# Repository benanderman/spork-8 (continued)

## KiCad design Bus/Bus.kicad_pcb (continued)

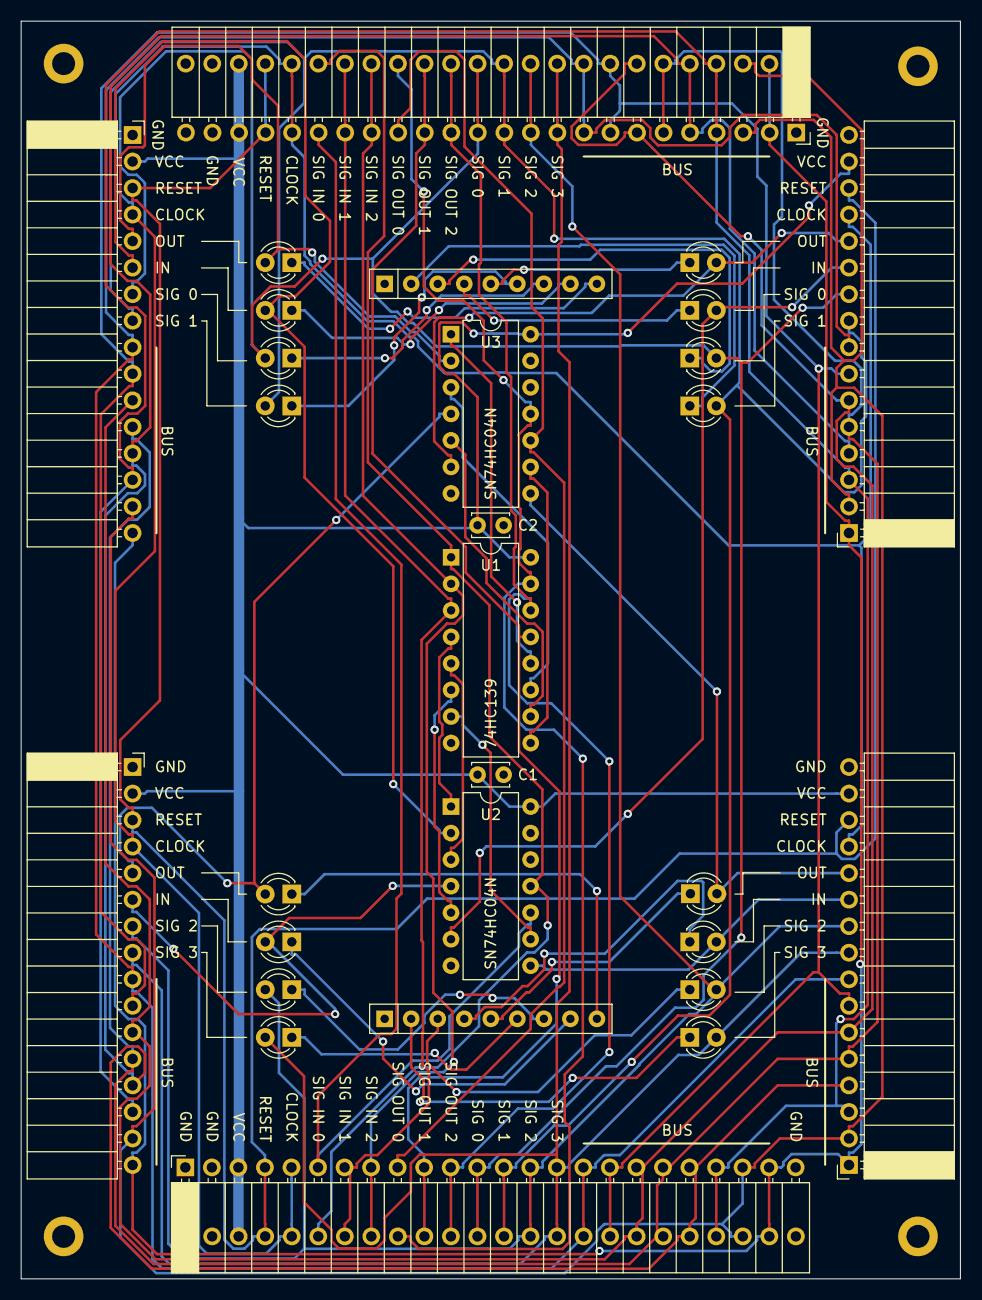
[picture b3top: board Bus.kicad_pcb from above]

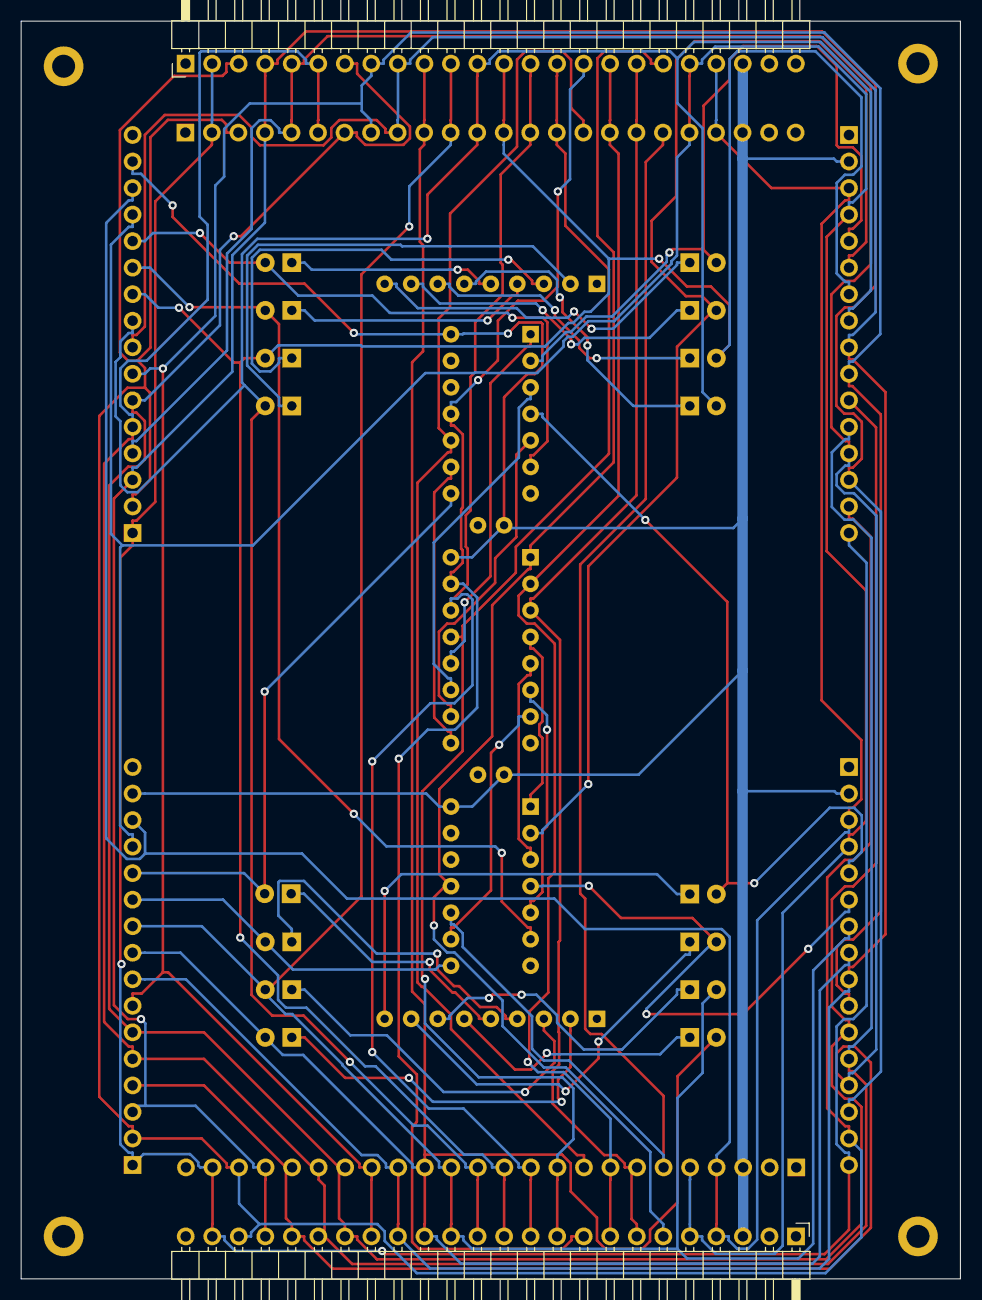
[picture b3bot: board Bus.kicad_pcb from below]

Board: 4 copper layers, 89.9 x 120.4 mm, 35 parts (2 on the bottom side), 56 nets.

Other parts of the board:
HOLE1, HOLE2, HOLE3, HOLE4: MountingHole_2.2mm_M2_DIN965_Pad

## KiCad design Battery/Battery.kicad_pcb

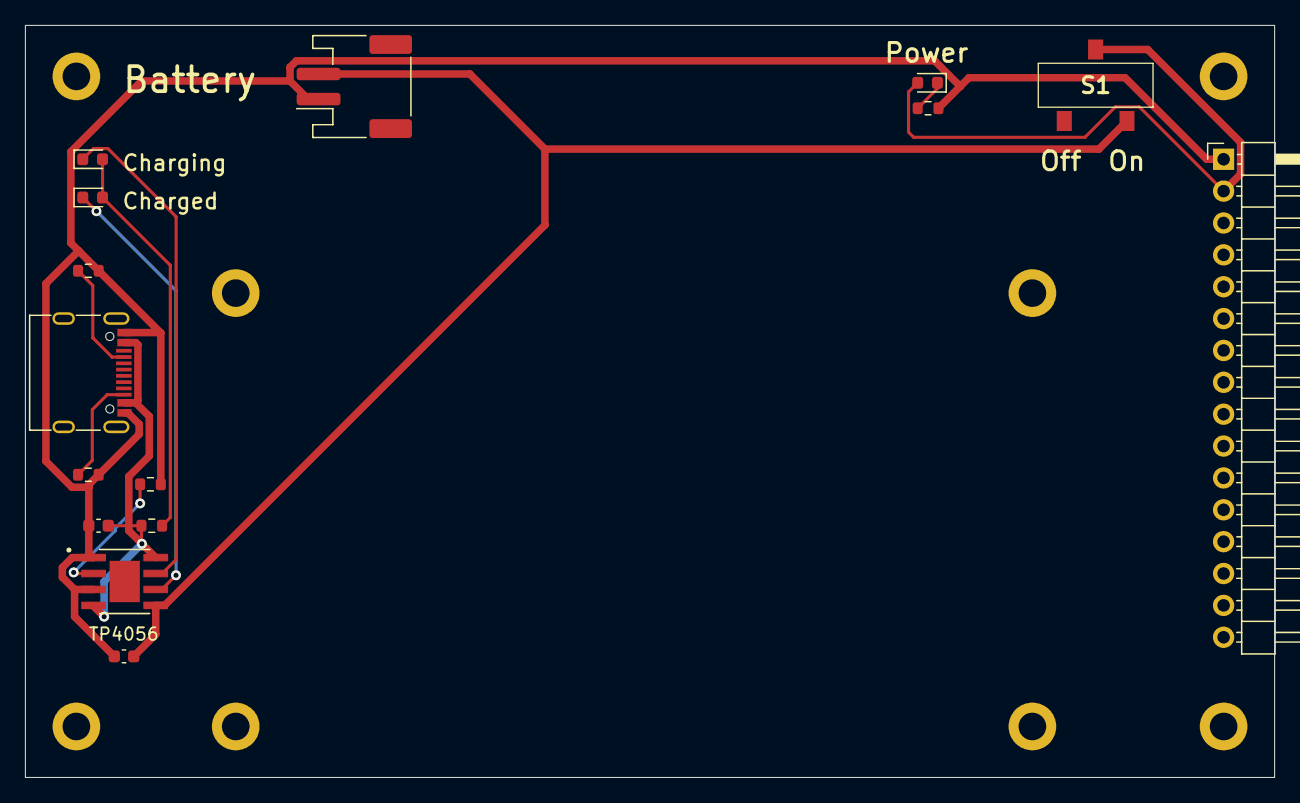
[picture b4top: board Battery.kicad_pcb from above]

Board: 2 copper layers, 99.6 x 59.9 mm, 23 parts (0 on the bottom side), 11 nets.

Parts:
BT1: Battery; JST_PH_S2B-PH-SM4-TB_1x02-1MP_P2.00mm_Horizontal
C1, C2: 10uF; C_0603_1608Metric
D1: GREEN; LED_0603_1608Metric
D2: RED; LED_0603_1608Metric
D3: LED; LED_0603_1608Metric
HOLE1, HOLE2, HOLE3, HOLE4, HOLE5, HOLE6, HOLE7, HOLE8: MountingHole_2.2mm_M2_DIN965_Pad
J1: Conn_01x16; PinHeader_1x16_P2.54mm_Horizontal
J4: USB_C_Receptacle_PowerOnly_6P; USB_C_Receptacle_G-Switch_GT-USB-7010ASV
R1: 1.2k; R_0603_1608Metric
R2, R5: 10k; R_0603_1608Metric
R3, R4: 5.1k; R_0603_1608Metric
S1: SS-3235D-03-L2; SS3235D03L2
U1: TP4056; SOP127P600X175-9N

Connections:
GND: BT1.1, C1.2, C2.2, J1.1, J4.A12 (GND), J4.B12 (GND), R1.1, R3.1, R4.1, R5.1, U1.1 (TEMP), U1.3 (GND)
unnamed: BT1.2, C2.1, S1.3, U1.5 (BAT)
unnamed: D1.2 (A), D2.2 (A), R2.1
unnamed: D1.1 (K), U1.6 (~STDBY)
unnamed: D2.1 (K), U1.7 (~CHRG)
unnamed: D3.1 (K), R5.2
unnamed: J4.A5 (CC1), R4.2
unnamed: J4.B5 (CC2), R3.2
unnamed: C1.1, J4.A9 (VBUS), J4.B9 (VBUS), R2.2, U1.4 (VCC), U1.8 (CE)
unnamed: R1.2, U1.2 (PROG)
VCC: D3.2 (A), J1.2, S1.2

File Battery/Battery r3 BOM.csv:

Designator,Comment,Footprint,LCSC Part Number
BT1,Battery,JST_PH_S2B-PH-SM4-TB_1x02-1MP_P2.00mm_Horizontal,C295747
"C1, C2",10uF,0603,C19702
D1,GREEN,0603,C965804
D2,RED,0603,C2286
D3,LED,0603,C72041
J1,Conn_01x16,PinHeader_1x16_P2.54mm_Horizontal,
J4,USB_C_Receptacle_PowerOnly_6P,USB_C_Receptacle_G-Switch_GT-USB-7010ASV,C2988369
R1,1.2k,0603,C22765
R2,10k,0603,C25804
"R3, R4",5.1k,0603,C23186
R5,10k,0603,C25804
S1,SS-3235D-03-L2,SS3235D03L2,C381097
U1,TP4056,SOP127P600X175-9N,C16581

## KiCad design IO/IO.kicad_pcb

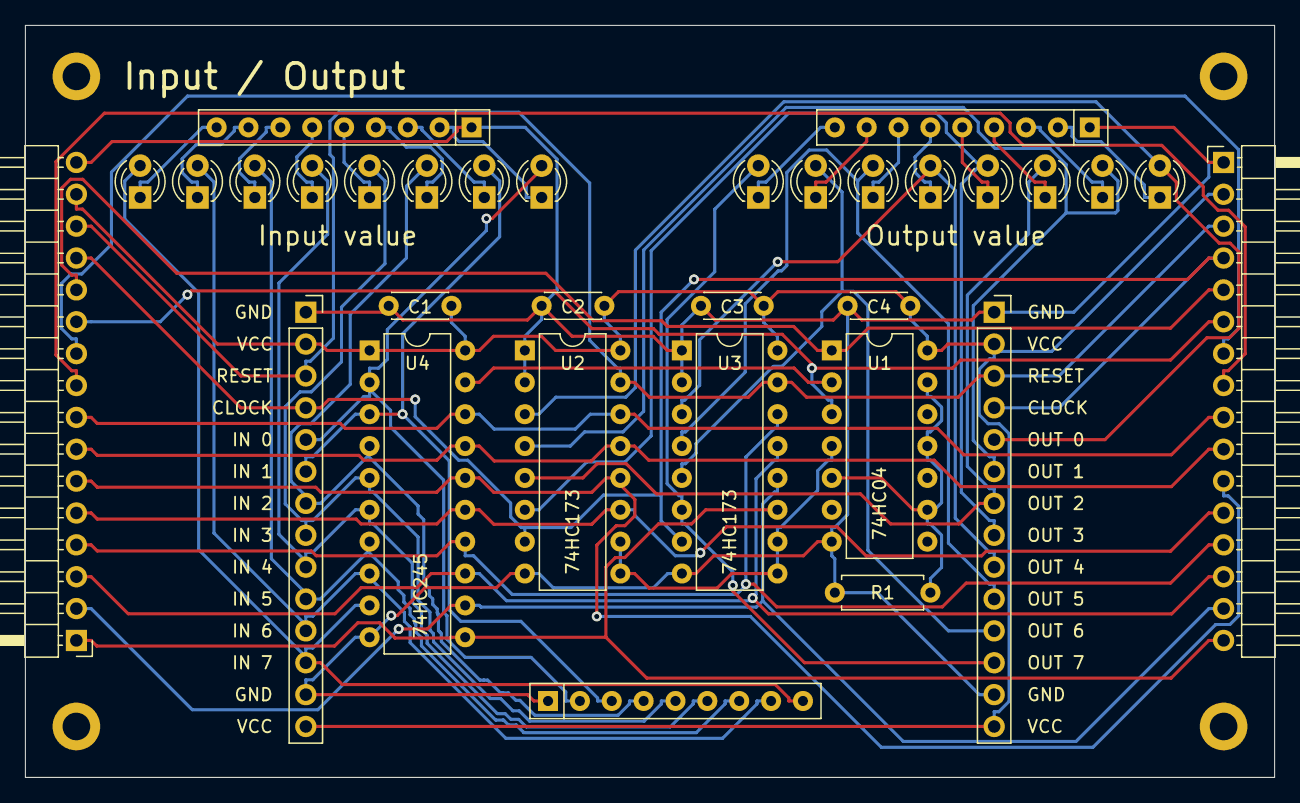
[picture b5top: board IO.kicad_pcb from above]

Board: 2 copper layers, 99.6 x 59.9 mm, 36 parts (0 on the bottom side), 51 nets.

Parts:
C1, C2, C3, C4: 100nF; C_Disc_D4.3mm_W1.9mm_P5.00mm
D1, D2, D3, D4, D5, D6, D7, D8, D9, D10, D11, D12, D13, D14, D15, D16: LED; LED_D3.0mm_Clear
HOLE1, HOLE2, HOLE3, HOLE4: MountingHole_2.2mm_M2_DIN965_Pad
J1, J2: Conn_01x16; PinHeader_1x16_P2.54mm_Horizontal
J3, J4: Conn_01x14; PinSocket_1x14_P2.54mm_Vertical
R1: 10k; R_Axial_DIN0207_L6.3mm_D2.5mm_P7.62mm_Horizontal
RN1, RN2: 1k; R_Array_SIP9
RN3: 100k; R_Array_SIP9
U1: 74HC04; DIP-14_W7.62mm
U2, U3: 74HC173; DIP-16_W7.62mm
U4: 74HC245; DIP-20_W7.62mm

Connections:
BUS0: J1.9, J2.8, U2.14 (D0), U4.18 (B0)
BUS1: J1.10, J2.7, U2.13 (D1), U4.17 (B1)
BUS2: J1.11, J2.6, U2.12 (D2), U4.16 (B2)
BUS3: J1.12, J2.5, U2.11 (D3), U4.15 (B3)
BUS4: J1.13, J2.4, U3.14 (D0), U4.14 (B4)
BUS5: J1.14, J2.3, U3.13 (D1), U4.13 (B5)
BUS6: J1.15, J2.2, U3.12 (D2), U4.12 (B6)
BUS7: J1.16, J2.1, U3.11 (D3), U4.11 (B7)
CLOCK: J1.4, J2.13, J3.4, J4.4, U2.7 (Cp), U3.7 (Cp)
GND: C1.2, C2.2, C3.2, C4.2, J1.1, J2.16, J3.1, J3.13, J4.1, J4.13, R1.1, RN1.1 (common), RN2.1 (common), RN3.1 (common), U1.7 (GND), U2.1 (Oe1), U2.2 (Oe2), U2.8 (GND), U3.1 (Oe1), U3.2 (Oe2), U3.8 (GND), U4.10 (GND)
IN0: D16.2 (A), J4.5, RN3.2 (R1), U4.2 (A0)
IN1: D15.2 (A), J4.6, RN3.3 (R2), U4.3 (A1)
IN2: D14.2 (A), J4.7, RN3.4 (R3), U4.4 (A2)
IN3: D13.2 (A), J4.8, RN3.5 (R4), U4.5 (A3)
IN4: D12.2 (A), J4.9, RN3.6 (R5), U4.6 (A4)
IN5: D11.2 (A), J4.10, RN3.7 (R6), U4.7 (A5)
IN6: D10.2 (A), J4.11, RN3.8 (R7), U4.8 (A6)
IN7: D9.2 (A), J4.12, RN3.9 (R8), U4.9 (A7)
unnamed: D1.1 (K), RN1.9 (R8)
unnamed: D2.1 (K), RN1.8 (R7)
unnamed: D3.1 (K), RN1.7 (R6)
unnamed: D4.1 (K), RN1.6 (R5)
unnamed: D5.1 (K), RN1.5 (R4)
unnamed: D6.1 (K), RN1.4 (R3)
unnamed: D7.1 (K), RN1.3 (R2)
unnamed: D8.1 (K), RN1.2 (R1)
unnamed: D9.1 (K), RN2.9 (R8)
unnamed: D10.1 (K), RN2.8 (R7)
unnamed: D11.1 (K), RN2.7 (R6)
unnamed: D12.1 (K), RN2.6 (R5)
unnamed: D13.1 (K), RN2.5 (R4)
unnamed: D14.1 (K), RN2.4 (R3)
unnamed: D15.1 (K), RN2.3 (R2)
unnamed: D16.1 (K), RN2.2 (R1)
unnamed: R1.2, U1.5, U1.9, U1.11, U1.13
R0: D8.2 (A), J3.5, U2.3 (Q0)
R1: D7.2 (A), J3.6, U2.4 (Q1)
R2: D6.2 (A), J3.7, U2.5 (Q2)
R3: D5.2 (A), J3.8, U2.6 (Q3)
R4: D4.2 (A), J3.9, U3.3 (Q0)
R5: D3.2 (A), J3.10, U3.4 (Q1)
R6: D2.2 (A), J3.11, U3.5 (Q2)
R7: D1.2 (A), J3.12, U3.6 (Q3)
RESET: J1.3, J2.14, J3.3, J4.3, U2.15 (Mr), U3.15 (Mr)
SIG0: J1.7, J2.10
SIG1: J1.8, J2.9
SIG_IN: J1.6, J2.11, U1.3
SIG_OUT: J1.5, J2.12, U1.1
VCC: C1.1, C2.1, C3.1, C4.1, J1.2, J2.15, J3.2, J3.14, J4.2, J4.14, U1.14 (VCC), U2.16 (VCC), U3.16 (VCC), U4.1 (A->B), U4.20 (VCC)
~SIG_IN: U1.4, U2.9 (E1), U2.10 (E2), U3.9 (E1), U3.10 (E2)
~SIG_OUT: U1.2, U4.19 (CE)

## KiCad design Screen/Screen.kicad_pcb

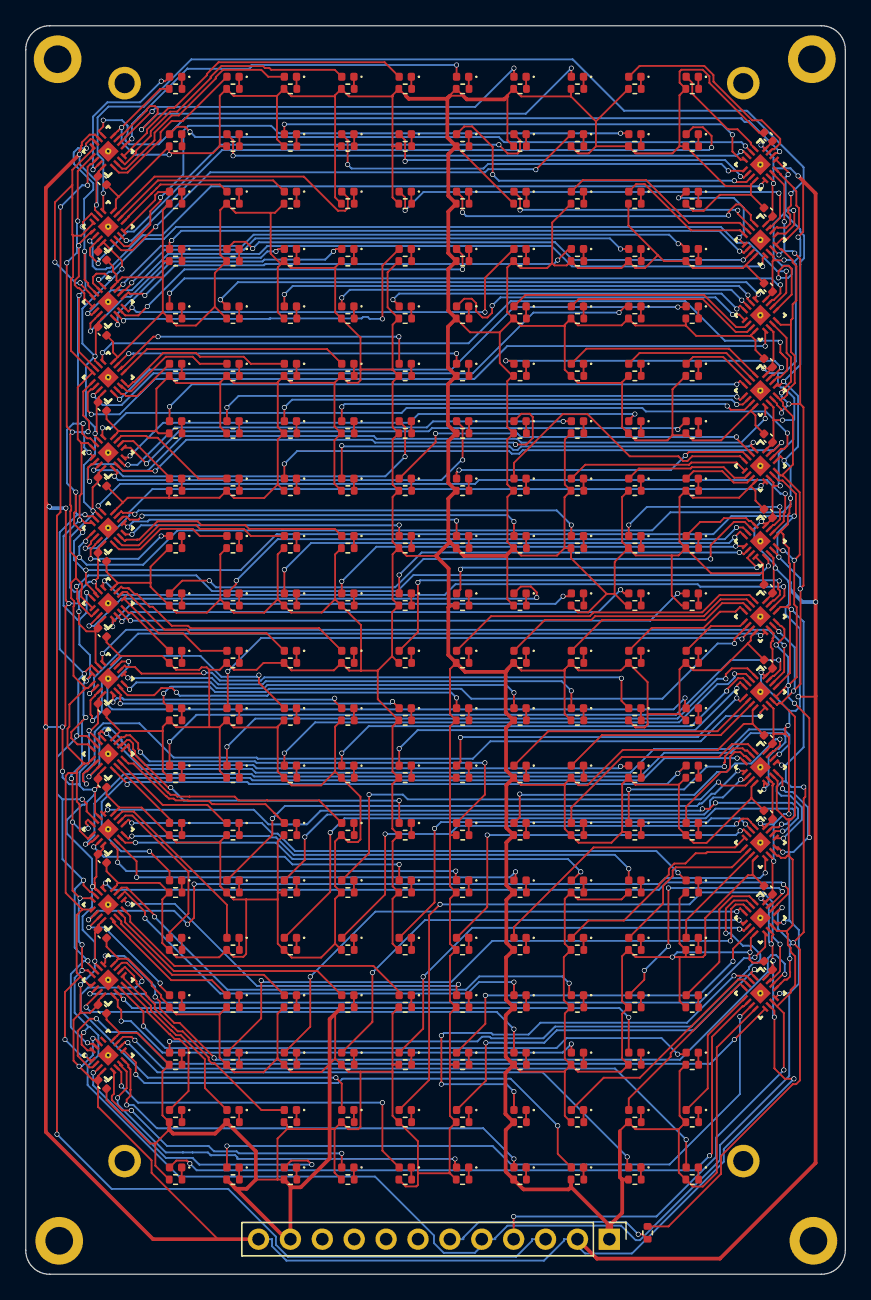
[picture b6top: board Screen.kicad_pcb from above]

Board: 2 copper layers, 65.3 x 99.4 mm, 460 parts (0 on the bottom side), 431 nets.

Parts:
C1, C2, C3, C4, C5, C6, C7, C8, C9, C10, C11, C12, C13, C14, C15, C16, C17, C18, C19, C20, C21, C22, C23, C24, C25: 0.1uF; C_0402_1005Metric
D1, D2, D3, D4, D5, D6, D7, D8, D9, D10, D11, D12, D13, D14, D15, D16, D17, D18, D19, D20, D21, D22, D23, D24, D25, D26, D27, D28, D29, D30, D31, D32, D33, D34, D35, D36, D37, D38, D39, D40, D41, D42, D43, D44, D45, D46, D47, D48, D49, D50, D51, D52, D53, D54, D55, D56, D57, D58, D59, D60, D61, D62, D63, D64, D65, D66, D67, D68, D69, D70, D71, D72, D73, D74, D75, D76, D77, D78, D79, D80, D81, D82, D83, D84, D85, D86, D87, D88, D89, D90, D91, D92, D93, D94, D95, D96, D97, D98, D99, D100, D101, D102, D103, D104, D105, D106, D107, D108, D109, D110, D111, D112, D113, D114, D115, D116, D117, D118, D119, D120, D121, D122, D123, D124, D125, D126, D127, D128, D129, D130, D131, D132, D133, D134, D135, D136, D137, D138, D139, D140, D141, D142, D143, D144, D145, D146, D147, D148, D149, D150, D151, D152, D153, D154, D155, D156, D157, D158, D159, D160, D161, D162, D163, D164, D165, D166, D167, D168, D169, D170, D171, D172, D173, D174, D175, D176, D177, D178, D179, D180, D181, D182, D183, D184, D185, D186, D187, D188, D189, D190, D191, D192, D193, D194, D195, D196, D197, D198, D199, D200: LED; LED_0402_1005Metric
HOLE1, HOLE2, HOLE3, HOLE4: MountingHole_1.6mm_M1.4_Pad
HOLE5, HOLE6, HOLE7, HOLE8: MountingHole_2.2mm_M2_DIN965_Pad
J1: Conn_01x12; PinHeader_1x12_P2.54mm_Vertical
R1, R2, R3, R4, R5, R6, R7, R8, R9, R10, R11, R12, R13, R14, R15, R16, R17, R18, R19, R20, R21, R22, R23, R24, R25, R26, R27, R28, R29, R30, R31, R32, R33, R34, R35, R36, R37, R38, R39, R40, R41, R42, R43, R44, R45, R46, R47, R48, R49, R50, R51, R52, R53, R54, R55, R56, R57, R58, R59, R60, R61, R62, R63, R64, R65, R66, R67, R68, R69, R70, R71, R72, R73, R74, R75, R76, R77, R78, R79, R80, R81, R82, R83, R84, R85, R86, R87, R88, R89, R90, R91, R92, R93, R94, R95, R96, R97, R98, R99, R100, R101, R102, R103, R104, R105, R106, R107, R108, R109, R110, R111, R112, R113, R114, R115, R116, R117, R118, R119, R120, R121, R122, R123, R124, R125, R126, R127, R128, R129, R130, R131, R132, R133, R134, R135, R136, R137, R138, R139, R140, R141, R142, R143, R144, R145, R146, R147, R148, R149, R150, R151, R152, R153, R154, R155, R156, R157, R158, R159, R160, R161, R162, R163, R164, R165, R166, R167, R168, R169, R170, R171, R172, R173, R174, R175, R176, R177, R178, R179, R180, R181, R182, R183, R184, R185, R186, R187, R188, R189, R190, R191, R192, R193, R194, R195, R196, R197, R198, R199, R200, R201: 10k; R_0402_1005Metric
U1, U2, U3, U4, U5, U6, U7, U8, U9, U10, U11, U12, U13, U14, U15, U16, U17, U18, U19, U20, U21, U22, U23, U24, U25: 74HC595; RWN0016A

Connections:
/LED_Row1/QH': U2.9 (QH'), U3.14 (SER)
/LED_Row2/QH': U3.9 (QH'), U4.14 (SER)
/LED_Row3/QH': U4.9 (QH'), U5.14 (SER)
/LED_Row4/QH': U5.9 (QH'), U6.14 (SER)
/LED_Row5/QH': U6.9 (QH'), U7.14 (SER)
/LED_Row6/QH': U7.9 (QH'), U8.14 (SER)
/LED_Row7/QH': U8.9 (QH'), U9.14 (SER)
/LED_Row8/QH': U9.9 (QH'), U10.14 (SER)
/LED_Row10/QH': U13.9 (QH'), U14.14 (SER)
/LED_Row10/SER: U12.9 (QH'), U13.14 (SER)
/LED_Row11/QH': U14.9 (QH'), U15.14 (SER)
/LED_Row12/QH': U15.9 (QH'), U16.14 (SER)
/LED_Row13/SER: U11.9 (QH'), U12.14 (SER)
/LED_Row14/SER: U10.9 (QH'), U11.14 (SER)
/LED_Row15/QH': U18.9 (QH'), U19.14 (SER)
/LED_Row15/SER: U17.9 (QH'), U18.14 (SER)
/LED_Row16/QH': U20.9 (QH'), U21.14 (SER)
/LED_Row16/SER: U19.9 (QH'), U20.14 (SER)
/LED_Row18/SER: U16.9 (QH'), U17.14 (SER)
/LED_Row20/QH': U21.9 (QH'), U22.14 (SER)
/LED_Row21/QH': U22.9 (QH'), U23.14 (SER)
/LED_Row22/QH': U24.9 (QH'), U25.14 (SER)
/LED_Row22/SER: U23.9 (QH'), U24.14 (SER)
/LED_Row/QH': U1.9 (QH'), U2.14 (SER)
DisplayOE: R201.1, U1.13 (~OE), U2.13 (~OE), U3.13 (~OE), U4.13 (~OE), U5.13 (~OE), U6.13 (~OE), U7.13 (~OE), U8.13 (~OE), U9.13 (~OE), U10.13 (~OE), U11.13 (~OE), U12.13 (~OE), U13.13 (~OE), U14.13 (~OE), U15.13 (~OE), U16.13 (~OE), U17.13 (~OE), U18.13 (~OE), U19.13 (~OE), U20.13 (~OE), U21.13 (~OE), U22.13 (~OE), U23.13 (~OE), U24.13 (~OE), U25.13 (~OE)
DisplayRCLK: J1.5, U1.12 (RCLK), U2.12 (RCLK), U3.12 (RCLK), U4.12 (RCLK), U5.12 (RCLK), U6.12 (RCLK), U7.12 (RCLK), U8.12 (RCLK), U9.12 (RCLK), U10.12 (RCLK), U11.12 (RCLK), U12.12 (RCLK), U13.12 (RCLK), U14.12 (RCLK), U15.12 (RCLK), U16.12 (RCLK), U17.12 (RCLK), U18.12 (RCLK), U19.12 (RCLK), U20.12 (RCLK), U21.12 (RCLK), U22.12 (RCLK), U23.12 (RCLK), U24.12 (RCLK), U25.12 (RCLK)
DisplaySER: J1.3, U1.14 (SER)
DisplaySRCLK: J1.4, U1.11 (SRCLK), U2.11 (SRCLK), U3.11 (SRCLK), U4.11 (SRCLK), U5.11 (SRCLK), U6.11 (SRCLK), U7.11 (SRCLK), U8.11 (SRCLK), U9.11 (SRCLK), U10.11 (SRCLK), U11.11 (SRCLK), U12.11 (SRCLK), U13.11 (SRCLK), U14.11 (SRCLK), U15.11 (SRCLK), U16.11 (SRCLK), U17.11 (SRCLK), U18.11 (SRCLK), U19.11 (SRCLK), U20.11 (SRCLK), U21.11 (SRCLK), U22.11 (SRCLK), U23.11 (SRCLK), U24.11 (SRCLK), U25.11 (SRCLK)
GND: C1.2, C2.2, C3.2, C4.2, C5.2, C6.2, C7.2, C8.2, C9.2, C10.2, C11.2, C12.2, C13.2, C14.2, C15.2, C16.2, C17.2, C18.2, C19.2, C20.2, C21.2, C22.2, C23.2, C24.2, C25.2, J1.1, J1.11, R1.1, R2.1, R3.1, R4.1, R5.1, R6.1, R7.1, R8.1, R9.1, R10.1, R11.1, R12.1, R13.1, R14.1, R15.1, R16.1, R17.1, R18.1, R19.1, R20.1, R21.1, R22.1, R23.1, R24.1, R25.1, R26.1, R27.1, R28.1, R29.1, R30.1, R31.1, R32.1, R33.1, R34.1, R35.1, R36.1, R37.1, R38.1, R39.1, R40.1, R41.1, R42.1, R43.1, R44.1, R45.1, R46.1, R47.1, R48.1, R49.1, R50.1, R51.1, R52.1, R53.1, R54.1, R55.1, R56.1, R57.1, R58.1, R59.1, R60.1, R61.1, R62.1, R63.1, R64.1, R65.1, R66.1, R67.1, R68.1, R69.1, R70.1, R71.1, R72.1, R73.1, R74.1, R75.1, R76.1, R77.1, R78.1, R79.1, R80.1, R81.1, R82.1, R83.1, R84.1, R85.1, R86.1, R87.1, R88.1, R89.1, R90.1, R91.1, R92.1, R93.1, R94.1, R95.1, R96.1, R97.1, R98.1, R99.1, R100.1, R101.1, R102.1, R103.1, R104.1, R105.1, R106.1, R107.1, R108.1, R109.1, R110.1, R111.1, R112.1, R113.1, R114.1, R115.1, R116.1, R117.1, R118.1, R119.1, R120.1, R121.1, R122.1, R123.1, R124.1, R125.1, R126.1, R127.1, R128.1, R129.1, R130.1, R131.1, R132.1, R133.1, R134.1, R135.1, R136.1, R137.1, R138.1, R139.1, R140.1, R141.1, R142.1, R143.1, R144.1, R145.1, R146.1, R147.1, R148.1, R149.1, R150.1, R151.1, R152.1, R153.1, R154.1, R155.1, R156.1, R157.1, R158.1, R159.1, R160.1, R161.1, R162.1, R163.1, R164.1, R165.1, R166.1, R167.1, R168.1, R169.1, R170.1, R171.1, R172.1, R173.1, R174.1, R175.1, R176.1, R177.1, R178.1, R179.1, R180.1, R181.1, R182.1, R183.1, R184.1, R185.1, R186.1, R187.1, R188.1, R189.1, R190.1, R191.1, R192.1, R193.1, R194.1, R195.1, R196.1, R197.1, R198.1, R199.1, R200.1, U1.8 (GND), U2.8 (GND), U3.8 (GND), U4.8 (GND), U5.8 (GND), U6.8 (GND), U7.8 (GND), U8.8 (GND), U9.8 (GND), U10.8 (GND), U11.8 (GND), U12.8 (GND), U13.8 (GND), U14.8 (GND), U15.8 (GND), U16.8 (GND), U17.8 (GND), U18.8 (GND), U19.8 (GND), U20.8 (GND), U21.8 (GND), U22.8 (GND), U23.8 (GND), U24.8 (GND), U25.8 (GND)
unnamed: D1.2 (A), U1.15 (QA)
unnamed: D1.1 (K), R1.2
unnamed: D2.2 (A), U1.1 (QB)
unnamed: D2.1 (K), R2.2
unnamed: D3.2 (A), U1.2 (QC)
unnamed: D3.1 (K), R3.2
unnamed: D4.2 (A), U1.3 (QD)
unnamed: D4.1 (K), R4.2
unnamed: D5.2 (A), U1.4 (QE)
unnamed: D5.1 (K), R5.2
unnamed: D6.2 (A), U1.5 (QF)
unnamed: D6.1 (K), R6.2
unnamed: D7.2 (A), U1.6 (QG)
unnamed: D7.1 (K), R7.2
unnamed: D8.2 (A), U1.7 (QH)
unnamed: D8.1 (K), R8.2
unnamed: D9.2 (A), U2.15 (QA)
unnamed: D9.1 (K), R9.2
unnamed: D10.2 (A), U2.1 (QB)
unnamed: D10.1 (K), R10.2
unnamed: D11.2 (A), U2.2 (QC)
unnamed: D11.1 (K), R11.2
unnamed: D12.2 (A), U2.3 (QD)
unnamed: D12.1 (K), R12.2
unnamed: D13.2 (A), U2.4 (QE)
unnamed: D13.1 (K), R13.2
unnamed: D14.2 (A), U2.5 (QF)
unnamed: D14.1 (K), R14.2
unnamed: D15.2 (A), U2.6 (QG)
unnamed: D15.1 (K), R15.2
unnamed: D16.2 (A), U2.7 (QH)
unnamed: D16.1 (K), R16.2
unnamed: D17.2 (A), U3.15 (QA)
unnamed: D17.1 (K), R17.2
unnamed: D18.2 (A), U3.1 (QB)
unnamed: D18.1 (K), R18.2
unnamed: D19.2 (A), U3.2 (QC)
unnamed: D19.1 (K), R19.2
unnamed: D20.2 (A), U3.3 (QD)
unnamed: D20.1 (K), R20.2
unnamed: D21.2 (A), U3.4 (QE)
unnamed: D21.1 (K), R21.2
unnamed: D22.2 (A), U3.5 (QF)
unnamed: D22.1 (K), R22.2
unnamed: D23.2 (A), U3.6 (QG)
unnamed: D23.1 (K), R23.2
unnamed: D24.2 (A), U3.7 (QH)
unnamed: D24.1 (K), R24.2
unnamed: D25.2 (A), U4.15 (QA)
unnamed: D25.1 (K), R25.2
unnamed: D26.2 (A), U4.1 (QB)
unnamed: D26.1 (K), R26.2
unnamed: D27.2 (A), U4.2 (QC)
unnamed: D27.1 (K), R27.2
unnamed: D28.2 (A), U4.3 (QD)
unnamed: D28.1 (K), R28.2
unnamed: D29.2 (A), U4.4 (QE)
unnamed: D29.1 (K), R29.2
unnamed: D30.2 (A), U4.5 (QF)
unnamed: D30.1 (K), R30.2
unnamed: D31.2 (A), U4.6 (QG)
unnamed: D31.1 (K), R31.2
unnamed: D32.2 (A), U4.7 (QH)
unnamed: D32.1 (K), R32.2
unnamed: D33.2 (A), U5.15 (QA)
unnamed: D33.1 (K), R33.2
unnamed: D34.2 (A), U5.1 (QB)
unnamed: D34.1 (K), R34.2
unnamed: D35.2 (A), U5.2 (QC)
unnamed: D35.1 (K), R35.2
unnamed: D36.2 (A), U5.3 (QD)
unnamed: D36.1 (K), R36.2
unnamed: D37.2 (A), U5.4 (QE)
unnamed: D37.1 (K), R37.2
unnamed: D38.2 (A), U5.5 (QF)
unnamed: D38.1 (K), R38.2
unnamed: D39.2 (A), U5.6 (QG)
unnamed: D39.1 (K), R39.2
unnamed: D40.2 (A), U5.7 (QH)
unnamed: D40.1 (K), R40.2
unnamed: D41.2 (A), U6.15 (QA)
unnamed: D41.1 (K), R41.2
unnamed: D42.2 (A), U6.1 (QB)
unnamed: D42.1 (K), R42.2
unnamed: D43.2 (A), U6.2 (QC)
unnamed: D43.1 (K), R43.2
unnamed: D44.2 (A), U6.3 (QD)
unnamed: D44.1 (K), R44.2
unnamed: D45.2 (A), U6.4 (QE)
unnamed: D45.1 (K), R45.2
unnamed: D46.2 (A), U6.5 (QF)
unnamed: D46.1 (K), R46.2
unnamed: D47.2 (A), U6.6 (QG)
unnamed: D47.1 (K), R47.2
unnamed: D48.2 (A), U6.7 (QH)
unnamed: D48.1 (K), R48.2
unnamed: D49.2 (A), U7.15 (QA)
unnamed: D49.1 (K), R49.2
unnamed: D50.2 (A), U7.1 (QB)
unnamed: D50.1 (K), R50.2
unnamed: D51.2 (A), U7.2 (QC)
unnamed: D51.1 (K), R51.2
unnamed: D52.2 (A), U7.3 (QD)
unnamed: D52.1 (K), R52.2
unnamed: D53.2 (A), U7.4 (QE)
unnamed: D53.1 (K), R53.2
unnamed: D54.2 (A), U7.5 (QF)
unnamed: D54.1 (K), R54.2
unnamed: D55.2 (A), U7.6 (QG)
unnamed: D55.1 (K), R55.2
unnamed: D56.2 (A), U7.7 (QH)
unnamed: D56.1 (K), R56.2
unnamed: D57.2 (A), U8.15 (QA)
unnamed: D57.1 (K), R57.2
unnamed: D58.2 (A), U8.1 (QB)
unnamed: D58.1 (K), R58.2
unnamed: D59.2 (A), U8.2 (QC)
unnamed: D59.1 (K), R59.2
unnamed: D60.2 (A), U8.3 (QD)
unnamed: D60.1 (K), R60.2
unnamed: D61.2 (A), U8.4 (QE)
unnamed: D61.1 (K), R61.2
unnamed: D62.2 (A), U8.5 (QF)
unnamed: D62.1 (K), R62.2
unnamed: D63.2 (A), U8.6 (QG)
unnamed: D63.1 (K), R63.2
unnamed: D64.2 (A), U8.7 (QH)
unnamed: D64.1 (K), R64.2
unnamed: D65.2 (A), U9.15 (QA)
unnamed: D65.1 (K), R65.2
unnamed: D66.2 (A), U9.1 (QB)
unnamed: D66.1 (K), R66.2
unnamed: D67.2 (A), U9.2 (QC)
unnamed: D67.1 (K), R67.2
unnamed: D68.2 (A), U9.3 (QD)
unnamed: D68.1 (K), R68.2
unnamed: D69.2 (A), U9.4 (QE)
unnamed: D69.1 (K), R69.2
unnamed: D70.2 (A), U9.5 (QF)
unnamed: D70.1 (K), R70.2
unnamed: D71.2 (A), U9.6 (QG)
unnamed: D71.1 (K), R71.2
unnamed: D72.2 (A), U9.7 (QH)
unnamed: D72.1 (K), R72.2
unnamed: D73.2 (A), U10.15 (QA)
unnamed: D73.1 (K), R73.2
unnamed: D74.2 (A), U10.1 (QB)
unnamed: D74.1 (K), R74.2
unnamed: D75.2 (A), U10.2 (QC)
unnamed: D75.1 (K), R75.2
unnamed: D76.2 (A), U10.3 (QD)
unnamed: D76.1 (K), R76.2
unnamed: D77.2 (A), U10.4 (QE)
unnamed: D77.1 (K), R77.2
unnamed: D78.2 (A), U10.5 (QF)
unnamed: D78.1 (K), R78.2
unnamed: D79.2 (A), U10.6 (QG)
unnamed: D79.1 (K), R79.2
unnamed: D80.2 (A), U10.7 (QH)
unnamed: D80.1 (K), R80.2
unnamed: D81.2 (A), U11.15 (QA)
unnamed: D81.1 (K), R81.2
unnamed: D82.2 (A), U11.1 (QB)
unnamed: D82.1 (K), R82.2
unnamed: D83.2 (A), U11.2 (QC)
unnamed: D83.1 (K), R83.2
unnamed: D84.2 (A), U11.3 (QD)
unnamed: D84.1 (K), R84.2
unnamed: D85.2 (A), U11.4 (QE)
unnamed: D85.1 (K), R85.2
unnamed: D86.2 (A), U11.5 (QF)
unnamed: D86.1 (K), R86.2
unnamed: D87.2 (A), U11.6 (QG)
unnamed: D87.1 (K), R87.2
unnamed: D88.2 (A), U11.7 (QH)
unnamed: D88.1 (K), R88.2
unnamed: D89.2 (A), U12.15 (QA)
unnamed: D89.1 (K), R89.2
unnamed: D90.2 (A), U12.1 (QB)
unnamed: D90.1 (K), R90.2
unnamed: D91.2 (A), U12.2 (QC)
unnamed: D91.1 (K), R91.2
unnamed: D92.2 (A), U12.3 (QD)
unnamed: D92.1 (K), R92.2
unnamed: D93.2 (A), U12.4 (QE)
unnamed: D93.1 (K), R93.2
unnamed: D94.2 (A), U12.5 (QF)
unnamed: D94.1 (K), R94.2
unnamed: D95.2 (A), U12.6 (QG)
unnamed: D95.1 (K), R95.2
unnamed: D96.2 (A), U12.7 (QH)
unnamed: D96.1 (K), R96.2
unnamed: D97.2 (A), U13.15 (QA)
unnamed: D97.1 (K), R97.2
unnamed: D98.2 (A), U13.1 (QB)
unnamed: D98.1 (K), R98.2
unnamed: D99.2 (A), U13.2 (QC)
unnamed: D99.1 (K), R99.2
unnamed: D100.2 (A), U13.3 (QD)
unnamed: D100.1 (K), R100.2
unnamed: D101.2 (A), U13.4 (QE)
unnamed: D101.1 (K), R101.2
unnamed: D102.2 (A), U13.5 (QF)
unnamed: D102.1 (K), R102.2
unnamed: D103.2 (A), U13.6 (QG)
unnamed: D103.1 (K), R103.2
unnamed: D104.2 (A), U13.7 (QH)
unnamed: D104.1 (K), R104.2
unnamed: D105.2 (A), U14.15 (QA)
unnamed: D105.1 (K), R105.2
unnamed: D106.2 (A), U14.1 (QB)
unnamed: D106.1 (K), R106.2
unnamed: D107.2 (A), U14.2 (QC)
unnamed: D107.1 (K), R107.2
unnamed: D108.2 (A), U14.3 (QD)
unnamed: D108.1 (K), R108.2
unnamed: D109.2 (A), U14.4 (QE)
unnamed: D109.1 (K), R109.2
unnamed: D110.2 (A), U14.5 (QF)
unnamed: D110.1 (K), R110.2
unnamed: D111.2 (A), U14.6 (QG)
unnamed: D111.1 (K), R111.2
unnamed: D112.2 (A), U14.7 (QH)
unnamed: D112.1 (K), R112.2
unnamed: D113.2 (A), U15.15 (QA)
unnamed: D113.1 (K), R113.2
unnamed: D114.2 (A), U15.1 (QB)
unnamed: D114.1 (K), R114.2
unnamed: D115.2 (A), U15.2 (QC)
unnamed: D115.1 (K), R115.2
unnamed: D116.2 (A), U15.3 (QD)
unnamed: D116.1 (K), R116.2
unnamed: D117.2 (A), U15.4 (QE)
unnamed: D117.1 (K), R117.2
unnamed: D118.2 (A), U15.5 (QF)
unnamed: D118.1 (K), R118.2
unnamed: D119.2 (A), U15.6 (QG)
unnamed: D119.1 (K), R119.2
unnamed: D120.2 (A), U15.7 (QH)
unnamed: D120.1 (K), R120.2
unnamed: D121.2 (A), U16.15 (QA)
unnamed: D121.1 (K), R121.2
unnamed: D122.2 (A), U16.1 (QB)
unnamed: D122.1 (K), R122.2
unnamed: D123.2 (A), U16.2 (QC)
unnamed: D123.1 (K), R123.2
unnamed: D124.2 (A), U16.3 (QD)
unnamed: D124.1 (K), R124.2
unnamed: D125.2 (A), U16.4 (QE)
unnamed: D125.1 (K), R125.2
unnamed: D126.2 (A), U16.5 (QF)
unnamed: D126.1 (K), R126.2
unnamed: D127.2 (A), U16.6 (QG)
unnamed: D127.1 (K), R127.2
unnamed: D128.2 (A), U16.7 (QH)
unnamed: D128.1 (K), R128.2
unnamed: D129.2 (A), U17.15 (QA)
unnamed: D129.1 (K), R129.2
unnamed: D130.2 (A), U17.1 (QB)
unnamed: D130.1 (K), R130.2
unnamed: D131.2 (A), U17.2 (QC)
unnamed: D131.1 (K), R131.2
unnamed: D132.2 (A), U17.3 (QD)
unnamed: D132.1 (K), R132.2
unnamed: D133.2 (A), U17.4 (QE)
unnamed: D133.1 (K), R133.2
unnamed: D134.2 (A), U17.5 (QF)
unnamed: D134.1 (K), R134.2
unnamed: D135.2 (A), U17.6 (QG)
unnamed: D135.1 (K), R135.2
unnamed: D136.2 (A), U17.7 (QH)
unnamed: D136.1 (K), R136.2
unnamed: D137.2 (A), U18.15 (QA)
unnamed: D137.1 (K), R137.2
unnamed: D138.2 (A), U18.1 (QB)
unnamed: D138.1 (K), R138.2
unnamed: D139.2 (A), U18.2 (QC)
unnamed: D139.1 (K), R139.2
unnamed: D140.2 (A), U18.3 (QD)
unnamed: D140.1 (K), R140.2
unnamed: D141.2 (A), U18.4 (QE)
unnamed: D141.1 (K), R141.2
unnamed: D142.2 (A), U18.5 (QF)
unnamed: D142.1 (K), R142.2
unnamed: D143.2 (A), U18.6 (QG)
unnamed: D143.1 (K), R143.2
unnamed: D144.2 (A), U18.7 (QH)
unnamed: D144.1 (K), R144.2
unnamed: D145.2 (A), U19.15 (QA)
unnamed: D145.1 (K), R145.2
unnamed: D146.2 (A), U19.1 (QB)
unnamed: D146.1 (K), R146.2
unnamed: D147.2 (A), U19.2 (QC)
unnamed: D147.1 (K), R147.2
unnamed: D148.2 (A), U19.3 (QD)
unnamed: D148.1 (K), R148.2
unnamed: D149.2 (A), U19.4 (QE)
unnamed: D149.1 (K), R149.2
unnamed: D150.2 (A), U19.5 (QF)
unnamed: D150.1 (K), R150.2
unnamed: D151.2 (A), U19.6 (QG)
unnamed: D151.1 (K), R151.2
unnamed: D152.2 (A), U19.7 (QH)
unnamed: D152.1 (K), R152.2
unnamed: D153.2 (A), U20.15 (QA)
unnamed: D153.1 (K), R153.2
unnamed: D154.2 (A), U20.1 (QB)
unnamed: D154.1 (K), R154.2
unnamed: D155.2 (A), U20.2 (QC)
unnamed: D155.1 (K), R155.2
unnamed: D156.2 (A), U20.3 (QD)
unnamed: D156.1 (K), R156.2
unnamed: D157.2 (A), U20.4 (QE)
unnamed: D157.1 (K), R157.2
unnamed: D158.2 (A), U20.5 (QF)
unnamed: D158.1 (K), R158.2
unnamed: D159.2 (A), U20.6 (QG)
unnamed: D159.1 (K), R159.2
unnamed: D160.2 (A), U20.7 (QH)
unnamed: D160.1 (K), R160.2
unnamed: D161.2 (A), U21.15 (QA)
unnamed: D161.1 (K), R161.2
unnamed: D162.2 (A), U21.1 (QB)
unnamed: D162.1 (K), R162.2
unnamed: D163.2 (A), U21.2 (QC)
unnamed: D163.1 (K), R163.2
unnamed: D164.2 (A), U21.3 (QD)
unnamed: D164.1 (K), R164.2
unnamed: D165.2 (A), U21.4 (QE)
unnamed: D165.1 (K), R165.2
unnamed: D166.2 (A), U21.5 (QF)
unnamed: D166.1 (K), R166.2
unnamed: D167.2 (A), U21.6 (QG)
unnamed: D167.1 (K), R167.2
unnamed: D168.2 (A), U21.7 (QH)
unnamed: D168.1 (K), R168.2
unnamed: D169.2 (A), U22.15 (QA)
unnamed: D169.1 (K), R169.2
unnamed: D170.2 (A), U22.1 (QB)
unnamed: D170.1 (K), R170.2
unnamed: D171.2 (A), U22.2 (QC)
unnamed: D171.1 (K), R171.2
unnamed: D172.2 (A), U22.3 (QD)
unnamed: D172.1 (K), R172.2
unnamed: D173.2 (A), U22.4 (QE)
unnamed: D173.1 (K), R173.2
unnamed: D174.2 (A), U22.5 (QF)
unnamed: D174.1 (K), R174.2
unnamed: D175.2 (A), U22.6 (QG)
unnamed: D175.1 (K), R175.2
unnamed: D176.2 (A), U22.7 (QH)
unnamed: D176.1 (K), R176.2
unnamed: D177.2 (A), U23.15 (QA)
unnamed: D177.1 (K), R177.2
unnamed: D178.2 (A), U23.1 (QB)
unnamed: D178.1 (K), R178.2
unnamed: D179.2 (A), U23.2 (QC)
unnamed: D179.1 (K), R179.2
unnamed: D180.2 (A), U23.3 (QD)
unnamed: D180.1 (K), R180.2
unnamed: D181.2 (A), U23.4 (QE)
unnamed: D181.1 (K), R181.2
unnamed: D182.2 (A), U23.5 (QF)
unnamed: D182.1 (K), R182.2
unnamed: D183.2 (A), U23.6 (QG)
unnamed: D183.1 (K), R183.2
unnamed: D184.2 (A), U23.7 (QH)
unnamed: D184.1 (K), R184.2
unnamed: D185.2 (A), U24.15 (QA)
unnamed: D185.1 (K), R185.2
unnamed: D186.2 (A), U24.1 (QB)
unnamed: D186.1 (K), R186.2
unnamed: D187.2 (A), U24.2 (QC)
unnamed: D187.1 (K), R187.2
unnamed: D188.2 (A), U24.3 (QD)
unnamed: D188.1 (K), R188.2
unnamed: D189.2 (A), U24.4 (QE)
unnamed: D189.1 (K), R189.2
unnamed: D190.2 (A), U24.5 (QF)
unnamed: D190.1 (K), R190.2
unnamed: D191.2 (A), U24.6 (QG)
unnamed: D191.1 (K), R191.2
unnamed: D192.2 (A), U24.7 (QH)
unnamed: D192.1 (K), R192.2
unnamed: D193.2 (A), U25.15 (QA)
unnamed: D193.1 (K), R193.2
unnamed: D194.2 (A), U25.1 (QB)
unnamed: D194.1 (K), R194.2
unnamed: D195.2 (A), U25.2 (QC)
unnamed: D195.1 (K), R195.2
unnamed: D196.2 (A), U25.3 (QD)
unnamed: D196.1 (K), R196.2
unnamed: D197.2 (A), U25.4 (QE)
unnamed: D197.1 (K), R197.2
unnamed: D198.2 (A), U25.5 (QF)
unnamed: D198.1 (K), R198.2
unnamed: D199.2 (A), U25.6 (QG)
unnamed: D199.1 (K), R199.2
unnamed: D200.2 (A), U25.7 (QH)
unnamed: D200.1 (K), R200.2
unnamed: J1.6, R201.2
VCC: C1.1, C2.1, C3.1, C4.1, C5.1, C6.1, C7.1, C8.1, C9.1, C10.1, C11.1, C12.1, C13.1, C14.1, C15.1, C16.1, C17.1, C18.1, C19.1, C20.1, C21.1, C22.1, C23.1, C24.1, C25.1, J1.2, J1.12, U1.10 (~SRCLR), U1.16 (VCC), U2.10 (~SRCLR), U2.16 (VCC), U3.10 (~SRCLR), U3.16 (VCC), U4.10 (~SRCLR), U4.16 (VCC), U5.10 (~SRCLR), U5.16 (VCC), U6.10 (~SRCLR), U6.16 (VCC), U7.10 (~SRCLR), U7.16 (VCC), U8.10 (~SRCLR), U8.16 (VCC), U9.10 (~SRCLR), U9.16 (VCC), U10.10 (~SRCLR), U10.16 (VCC), U11.10 (~SRCLR), U11.16 (VCC), U12.10 (~SRCLR), U12.16 (VCC), U13.10 (~SRCLR), U13.16 (VCC), U14.10 (~SRCLR), U14.16 (VCC), U15.10 (~SRCLR), U15.16 (VCC), U16.10 (~SRCLR), U16.16 (VCC), U17.10 (~SRCLR), U17.16 (VCC), U18.10 (~SRCLR), U18.16 (VCC), U19.10 (~SRCLR), U19.16 (VCC), U20.10 (~SRCLR), U20.16 (VCC), U21.10 (~SRCLR), U21.16 (VCC), U22.10 (~SRCLR), U22.16 (VCC), U23.10 (~SRCLR), U23.16 (VCC), U24.10 (~SRCLR), U24.16 (VCC), U25.10 (~SRCLR), U25.16 (VCC)

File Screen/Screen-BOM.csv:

Comment,Designator,Footprint,LCSC Part Number
0.1uF,"C1, C2, C3, C4, C5, C6, C7, C8, C9, C10, C11, C12, C13, C14, C15, C16, C17, C18, C19, C20, C21, C22, C23, C24, C25",C_0402_1005Metric,C307331
LED,"D1, D2, D3, D4, D5, D6, D7, D8, D9, D10, D11, D12, D13, D14, D15, D16, D17, D18, D19, D20, D21, D22, D23, D24, D25, D26, D27, D28, D29, D30, D31, D32, D33, D34, D35, D36, D37, D38, D39, D40, D41, D42, D43, D44, D45, D46, D47, D48, D49, D50, D51, D52, D53, D54, D55, D56, D57, D58, D59, D60, D61, D62, D63, D64, D65, D66, D67, D68, D69, D70, D71, D72, D73, D74, D75, D76, D77, D78, D79, D80, D81, D82, D83, D84, D85, D86, D87, D88, D89, D90, D91, D92, D93, D94, D95, D96, D97, D98, D99, D100, D101, D102, D103, D104, D105, D106, D107, D108, D109, D110, D111, D112, D113, D114, D115, D116, D117, D118, D119, D120, D121, D122, D123, D124, D125, D126, D127, D128, D129, D130, D131, D132, D133, D134, D135, D136, D137, D138, D139, D140, D141, D142, D143, D144, D145, D146, D147, D148, D149, D150, D151, D152, D153, D154, D155, D156, D157, D158, D159, D160, D161, D162, D163, D164, D165, D166, D167, D168, D169, D170, D171, D172, D173, D174, D175, D176, D177, D178, D179, D180, D181, D182, D183, D184, D185, D186, D187, D188, D189, D190, D191, D192, D193, D194, D195, D196, D197, D198, D199, D200",LED_0402_1005Metric,C965793
Conn_01x12,J1,PinHeader_1x12_P2.54mm_Vertical,
10k,"R1, R2, R3, R4, R5, R6, R7, R8, R9, R10, R11, R12, R13, R14, R15, R16, R17, R18, R19, R20, R21, R22, R23, R24, R25, R26, R27, R28, R29, R30, R31, R32, R33, R34, R35, R36, R37, R38, R39, R40, R41, R42, R43, R44, R45, R46, R47, R48, R49, R50, R51, R52, R53, R54, R55, R56, R57, R58, R59, R60, R61, R62, R63, R64, R65, R66, R67, R68, R69, R70, R71, R72, R73, R74, R75, R76, R77, R78, R79, R80, R81, R82, R83, R84, R85, R86, R87, R88, R89, R90, R91, R92, R93, R94, R95, R96, R97, R98, R99, R100, R101, R102, R103, R104, R105, R106, R107, R108, R109, R110, R111, R112, R113, R114, R115, R116, R117, R118, R119, R120, R121, R122, R123, R124, R125, R126, R127, R128, R129, R130, R131, R132, R133, R134, R135, R136, R137, R138, R139, R140, R141, R142, R143, R144, R145, R146, R147, R148, R149, R150, R151, R152, R153, R154, R155, R156, R157, R158, R159, R160, R161, R162, R163, R164, R165, R166, R167, R168, R169, R170, R171, R172, R173, R174, R175, R176, R177, R178, R179, R180, R181, R182, R183, R184, R185, R186, R187, R188, R189, R190, R191, R192, R193, R194, R195, R196, R197, R198, R199, R200, R201",R_0402_1005Metric,C25744
74HC595,"U1, U2, U3, U4, U5, U6, U7, U8, U9, U10, U11, U12, U13, U14, U15, U16, U17, U18, U19, U20, U21, U22, U23, U24, U25",RWN0016A,C2682068

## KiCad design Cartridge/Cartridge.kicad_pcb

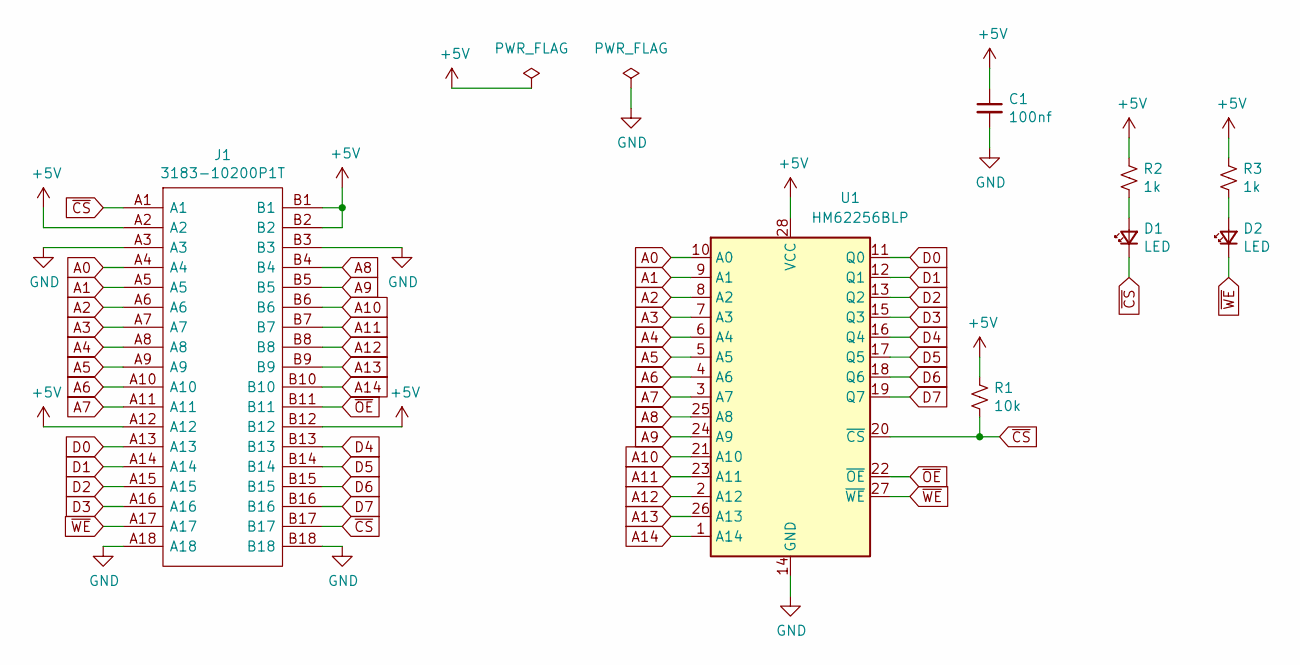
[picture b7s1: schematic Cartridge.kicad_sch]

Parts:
C1: 100nf; C_0603_1608Metric
D1, D2: LED; LED_0603_1608Metric
J1: 3183-10200P1T; BUS_PCIexpress_x1; Manufacturer_Part_Number 3183-10200P1T
R1: 10k; R_0603_1608Metric
R2, R3: 1k; R_0603_1608Metric
U1: HM62256BLP; SOIC-28W_7.5x17.9mm_P1.27mm

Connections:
+5V: C1.1, J1.A2, J1.A12, J1.B1, J1.B2, J1.B12, R1.1, R2.1, R3.1, U1.28 (VCC)
A0: J1.A4, U1.10 (A0)
A1: J1.A5, U1.9 (A1)
A2: J1.A6, U1.8 (A2)
A3: J1.A7, U1.7 (A3)
A4: J1.A8, U1.6 (A4)
A5: J1.A9, U1.5 (A5)
A6: J1.A10, U1.4 (A6)
A7: J1.A11, U1.3 (A7)
A8: J1.B4, U1.25 (A8)
A9: J1.B5, U1.24 (A9)
A10: J1.B6, U1.21 (A10)
A11: J1.B7, U1.23 (A11)
A12: J1.B8, U1.2 (A12)
A13: J1.B9, U1.26 (A13)
A14: J1.B10, U1.1 (A14)
D0: J1.A13, U1.11 (Q0)
D1: J1.A14, U1.12 (Q1)
D2: J1.A15, U1.13 (Q2)
D3: J1.A16, U1.15 (Q3)
D4: J1.B13, U1.16 (Q4)
D5: J1.B14, U1.17 (Q5)
D6: J1.B15, U1.18 (Q6)
D7: J1.B16, U1.19 (Q7)
GND: C1.2, J1.A3, J1.A18, J1.B3, J1.B18, U1.14 (GND)
unnamed: D1.2 (A), R2.2
unnamed: D2.2 (A), R3.2
~CS: D1.1 (K), J1.A1, J1.B17, R1.2, U1.20 (~CS)
~OE: J1.B11, U1.22 (~OE)
~WE: D2.1 (K), J1.A17, U1.27 (~WE)
